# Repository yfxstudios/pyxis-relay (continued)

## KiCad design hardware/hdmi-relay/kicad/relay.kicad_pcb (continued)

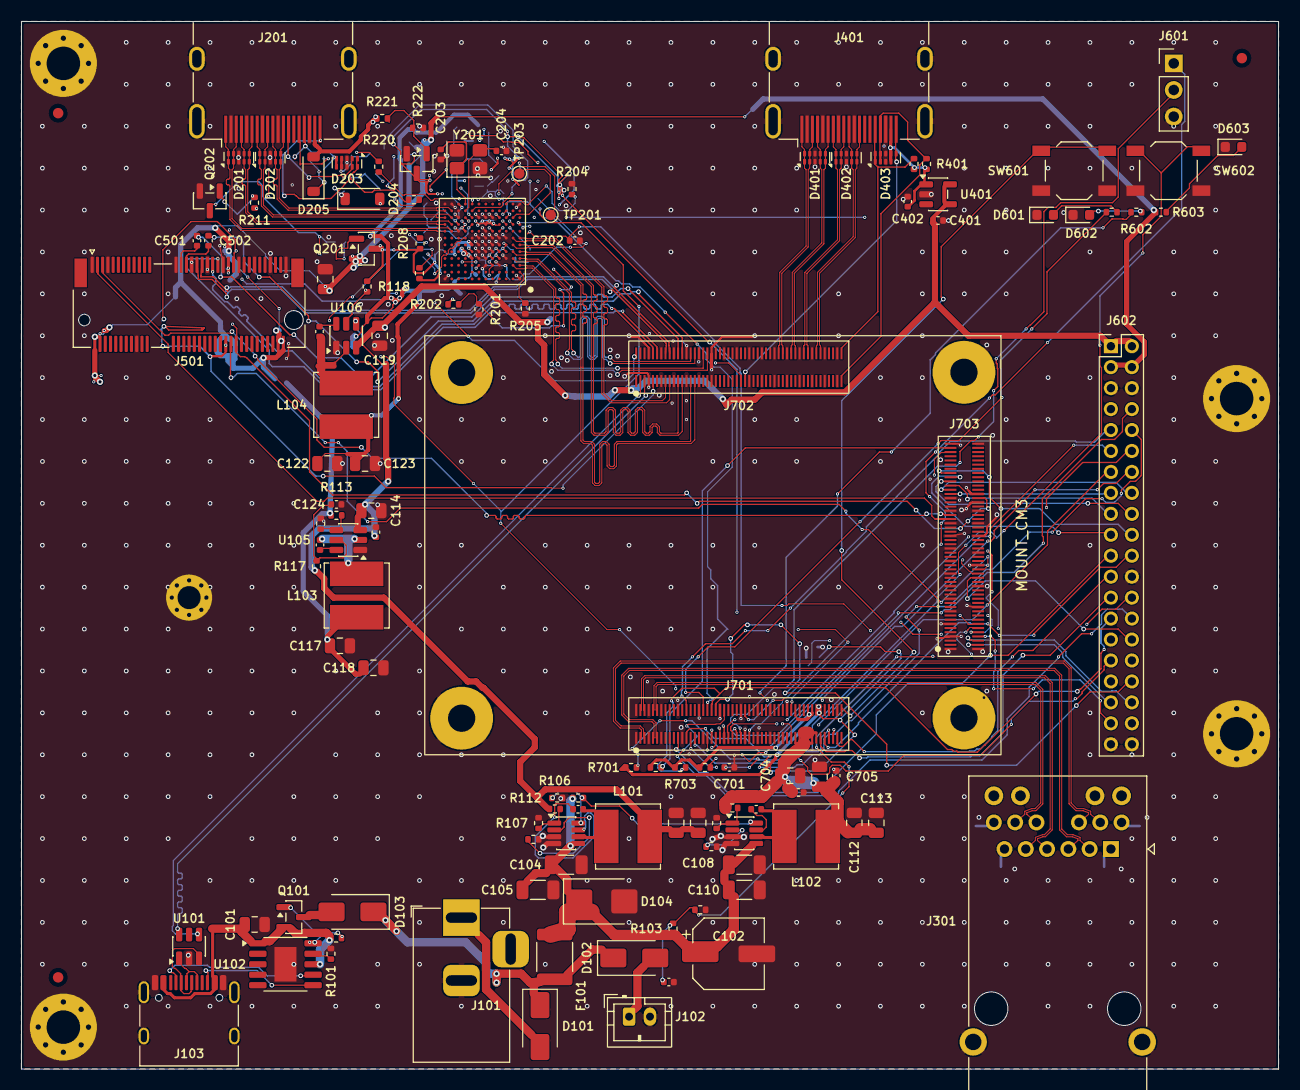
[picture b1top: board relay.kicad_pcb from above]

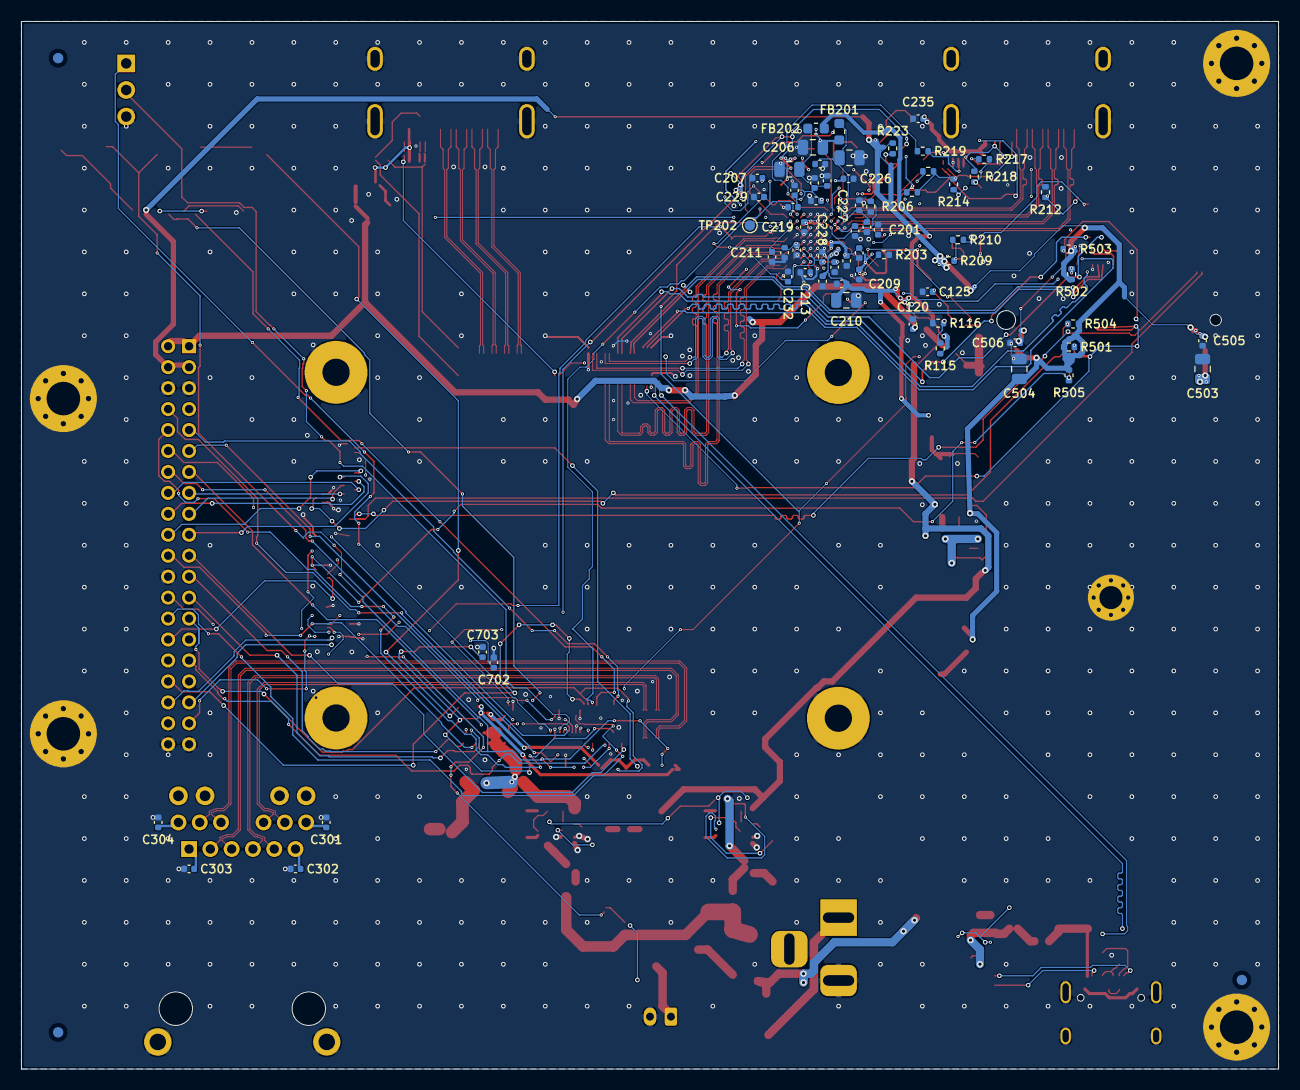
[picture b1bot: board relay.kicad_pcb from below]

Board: 4 copper layers, 120.0 x 100.0 mm, 198 parts (68 on the bottom side), 170 nets.

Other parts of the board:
C301, C302, C303, C304: 1uF; C_0402_1005Metric
FID1, FID2, FID3, FID4, FID5, FID6: Fiducial_1mm_Mask2mm
J301: RJ45 1000BASE-T magjack; RJ45_Pulse_JK0654219NL_Horizontal
MOUNT_CM3: Radxa CM3; Radxa_CM3_Mount

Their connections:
/Ethernet/CT1: C301.1, J301.12
/Ethernet/CT2: C302.1, J301.6
/Ethernet/CT3: C303.1, J301.1
/Ethernet/CT4: C304.1, J301.7
GND: C301.2, C302.2, C303.2, C304.2, J301.SH, MOUNT_CM3.MH1, MOUNT_CM3.MH2, MOUNT_CM3.MH3, MOUNT_CM3.MH4; also elsewhere on the board
MDI0_N: J301.10; also elsewhere on the board
MDI0_P: J301.11; also elsewhere on the board
MDI1_N: J301.5; also elsewhere on the board
MDI1_P: J301.4; also elsewhere on the board
MDI2_N: J301.2; also elsewhere on the board
MDI2_P: J301.3; also elsewhere on the board
MDI3_N: J301.9; also elsewhere on the board
MDI3_P: J301.8; also elsewhere on the board

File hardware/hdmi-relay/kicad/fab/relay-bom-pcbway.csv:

Line#,Qty,Designator,MPN,Manufacturer,Description,Package,Type,LCSC
1,1,C101,CL21B105KBFNNNE,Samsung Electro-Mechanics,1uF/50V: CAP CER 1uF 50V X7R 0805,C_0805_2012Metric,SMD,C28323
2,1,C102,RVT35V47M6X8,JIERR,47uF/35V: CAP ALUM 47uF ±20% 35V SMD,CP_Elec_6.3x7.7,SMD,C47023116
3,37,"C103,C115,C116,C120,C121,C124,C125,C201,C202,C207,C208,C209,C211,C212,C213,C214,C215,C216,C217,C218,C219,C223,C224,C225,C227,C228,C229,C230,C231,C232,C235,C505,C506,C702,C703,C706,C707",CL05B104KB54PNC,Samsung Electro-Mechanics,100nF: CAP CER 100nF 50V X7R 0402,C_0402_1005Metric,SMD,C307331
4,4,"C104,C105,C109,C110",1206B475K500NT,FH,4.7uF/50V: CAP CER 4.7uF 50V X7R 1206,C_1206_3216Metric,SMD,C29823
5,2,"C106,C111",CL05B103KB5NNNC,Samsung Electro-Mechanics,10nF: CAP CER 10nF 50V X7R 0402,C_0402_1005Metric,SMD,C15195
6,12,"C107,C108,C112,C113,C117,C118,C122,C123,C503,C504,C704,C705",CL21A226MAQNNNE,Samsung Electro-Mechanics,22uF/10V: CAP CER 22uF 25V X5R 0805,C_0805_2012Metric,SMD,C45783
7,7,"C114,C119,C205,C206,C210,C222,C234",CL21A106KAYNNNE,Samsung Electro-Mechanics,10uF/10V: CAP CER 10uF 25V X5R 0805,C_0805_2012Metric,SMD,C15850
8,2,"C203,C204",0402CG180J500NT,FH,18pF: CAP CER 18pF 50V C0G 0402,C_0402_1005Metric,SMD,C1549
9,10,"C220,C221,C226,C233,C301,C302,C303,C304,C401,C402",CL05A105KA5NQNC,Samsung Electro-Mechanics,1uF: CAP CER 1uF 25V X5R 0402,C_0402_1005Metric,SMD,C52923
10,2,"C501,C502",0402WGF0000TCE,UNI-ROYAL,0R: RES 0R jumper 62.5mW 0402,C_0402_1005Metric,SMD,C17168
11,1,C701,0402B102K500NT,FH,1nF: CAP CER 1nF 50V X7R 0402,C_0402_1005Metric,SMD,C1523
12,3,"D101,D102,D103",SS54,MDD(Microdiode Semiconductor),SS54: DIODE SCHOTTKY 40V SMA(DO-214AC),D_SMA,SMD,C22452
13,1,D104,SMBJ20CA,MDD(Microdiode Semiconductor),SMBJ20CA: TVS DIODE 20VWM 32.4VC DO-214AA(SMB),D_SMB,SMD,C113992
14,6,"D201,D202,D203,D401,D402,D403",RCLAMP0524P,TECH PUBLIC,RCLAMP0524P: ESD DIODE 5VWM 17VC DFN2510-10,USON-10_2.5x1.0mm_P0.5mm,SMD,C907837
15,2,"D204,D205",MBR0530T1G,onsemi,MBR0530: DIODE SCHOTTKY 30V SOD-123,D_SOD-123,SMD,C82046
16,1,D601,KT-0603W,Hubei KENTO Elec,white: LED WHITE 0603 SMD,LED_0603_1608Metric,SMD,C2290
17,1,D602,KT-0603B,Hubei KENTO Elec,blue: LED BLUE WATER CLEAR 0603 SMD,LED_0603_1608Metric,SMD,C2288
18,1,D603,KT-0603R,Hubei KENTO Elec,red PWR: LED RED WATER CLEAR 0603 SMD,LED_0603_1608Metric,SMD,C2286
19,1,F101,1812L300/30GR,LUTE,3A hold: PTC RESET FUSE 30V 3A 1812,Fuse_1812_4532Metric,SMD,C48985875
20,2,"FB201,FB202",MPZ1608S331ATA00,TDK,330R@100MHz: FERRITE BEAD 330Ω 0603 1LN,L_0603_1608Metric,SMD,C275487
21,1,J101,PJ-002AH,CUI,DC 6-17V: Right Angle DC Power Jack -25℃~+85℃ 2mm 6.5mm 5A 24V Through Hole Power Connectors RoHS,BarrelJack_Horizontal,THT,C2961147
22,1,J102,B2B-PH-K-S(LF)(SN),JST,NP-F plate: CONN HEADER TH 2POS 2mm,JST_PH_B2B-PH-K_1x02_P2.00mm_Vertical,THT,C131337
23,1,J103,TYPE-C-31-M-12,Korean Hroparts Elec,USB_C_Receptacle_USB2.0_16P: CONN RCPT Type-C 16POS SMD,USB_C_Receptacle_HRO_TYPE-C-31-M-12,SMD,C165948
24,2,"J201,J401",2086581001,MOLEX,HDMI IN: HDMI FOR INSERT-MOLD TYPE,HDMI_A_Molex_208658-1001_Horizontal,SMD,C916313
25,1,J501,2199230-4,TE Connectivity,M.2 E-key 2230: CONN 67POS 0.5mm SMD R/A,TE_M.2_E_2x38-1MP_P0.5mm,SMD,C2977809
26,1,J601,PZ254V-11-03P,XFCN,DEBUG UART 3V3: CONN HEADER 3POS 2.54mm SINGLE ROW TH,PinHeader_1x03_P2.54mm_Vertical,THT,C2937625
27,3,"J701,J702,J703",DF40C-100DS-0.4V(51),HRS,"CM3 J69: 0.4mm Pitch, 1.5 to 4.0mm Height, Board-to-Board and Board-to-FPC Connectors",Radxa_CM3_J69,SMD,C597931
28,2,"L101,L102",SRN6045TA-6R8M,BOURNS,"6.8uH 3.6A: FIXED IND 6.8uH 3.6A 34mΩ SMD,6x6mm",L_Bourns_SRN6045TA,SMD,C2041457
29,1,L103,SWPA6045S2R2NT,Sunlord,2.2uH: 2.2uH 4.6A 18mOhm ±30% 6x6 shielded power inductor,L_Bourns_SRN6045TA,SMD,C36500
30,1,L104,SWPA6045S1R5NT,Sunlord,1.5uH: 1.5uH 4.95A 12mOhm ±30% 6x6 shielded power inductor,L_Bourns_SRN6045TA,SMD,C96956
31,2,"Q101,Q201",AO3401A,AOS,AO3401A: MOSFET P-CH 30V 4A SOT-23,SOT-23,SMD,C15127
32,2,"Q202,Q203",MMBT3904(RANGE:100-300),JSCJ,MMBT3904: TRANS NPN 40V 200mA SOT-23,SOT-23,SMD,C20526
33,1,R101,0402WGF6801TCE,UNI-ROYAL,6.8k: RES 6.8kΩ ±1% 62.5mW 0402,R_0402_1005Metric,SMD,C25917
34,5,"R102,R103,R111,R117,R212",0402WGF1003TCE,UNI-ROYAL,100k: RES 100kΩ ±1% 62.5mW 0402,R_0402_1005Metric,SMD,C25741
35,11,"R104,R114,R115,R118,R201,R209,R222,R223,R504,R701,R702",0402WGF1002TCE,UNI-ROYAL,10k: RES 10kΩ ±1% 62.5mW 0402,R_0402_1005Metric,SMD,C25744
36,2,"R105,R108",0402WGF2003TCE,UNI-ROYAL,200k: RES 200k 1% 62.5mW 0402,R_0402_1005Metric,SMD,C25764
37,2,"R106,R109",0402WGF1103TCE,UNI-ROYAL,110k: RES 110kΩ ±1% 62.5mW 0402,R_0402_1005Metric,SMD,C25745
38,2,"R107,R110",0402WGF1502TCE,UNI-ROYAL,15k: RES 15kΩ ±1% 62.5mW 0402,R_0402_1005Metric,SMD,C25756
39,1,R112,0402WGF3902TCE,UNI-ROYAL,39k: RES 39kΩ ±1% 62.5mW 0402,R_0402_1005Metric,SMD,C25783
40,1,R113,0402WGF3302TCE,UNI-ROYAL,33k: RES 33kΩ ±1% 62.5mW 0402,R_0402_1005Metric,SMD,C25779
41,1,R116,0402WGF2322TCE,UNI-ROYAL,23.2k: RES 23.2kΩ ±1% 62.5mW 0402,R_0402_1005Metric,SMD,C25873
42,3,"R203,R204,R221",0402WGF2001TCE,UNI-ROYAL,2k 1%: RES 2kΩ ±1% 62.5mW 0402,R_0402_1005Metric,SMD,C4109
43,1,R205,0402WGF4021TCE,UNI-ROYAL,4.02k 1%: RES 4.02kΩ ±1% 62.5mW 0402,R_0402_1005Metric,SMD,C43251
44,1,R206,0402WGF1000TCE,UNI-ROYAL,100R: RES 100Ω ±1% 62.5mW 0402,R_0402_1005Metric,SMD,C25076
45,2,"R207,R208",0402WGF4701TCE,UNI-ROYAL,4.7k: RES 4.7kΩ ±1% 62.5mW 0402,R_0402_1005Metric,SMD,C25900
46,2,"R210,R211",0402WGF1001TCE,UNI-ROYAL,1k: RES 1kΩ ±1% 62.5mW 0402,R_0402_1005Metric,SMD,C11702
47,4,"R213,R215,R219,R220",0402WGF220JTCE,UNI-ROYAL,22R: RES 22Ω ±1% 62.5mW 0402,R_0402_1005Metric,SMD,C25092
48,1,R214,0402WGF2702TCE,UNI-ROYAL,27k: RES 27kΩ ±1% 62.5mW 0402,R_0402_1005Metric,SMD,C25771
49,2,"R217,R218",0402WGF4702TCE,UNI-ROYAL,47k: RES 47kΩ ±1% 62.5mW 0402,R_0402_1005Metric,SMD,C25792
50,5,"R401,R402,R603,R703,R704",0402WGF2201TCE,UNI-ROYAL,2.2k: RES 2.2kΩ ±1% 62.5mW 0402,R_0402_1005Metric,SMD,C25879
51,2,"R601,R602",0402WGF1500TCE,UNI-ROYAL,150R: RES 150R 1% 62.5mW 0402,R_0402_1005Metric,SMD,C25082
52,2,"SW601,SW602",TL3342F160QG,E-Switch,RESET: SWITCH TACTILE SPST 160gf SMD,SW_SPST_TL3342,SMD,C2886898
53,1,U101,USBLC6-2SC6,UMW,USBLC6-2SC6: ESD DIODE 15VC SOT-23-6,SOT-23-6,SMD,C2687116
54,1,U102,CH224A,WCH,CH224A: Power Receiver Controller 1C 140W ESSOP-10 Power Management - Specialized ,SSOP-10-1EP_3.9x4.9mm_P1mm_EP2.1x3.3mm,SMD,C42459160
55,2,"U103,U104",SY8303AIC,Silergy,"SY8303AIC: High Efficiency Fast Response, 3A, 40V Input Synchronous Step Down Regulator",TSOT-23-8,SMD,C97054
56,2,"U105,U106",TPS563201DDCR,TI,"TPS563201: 4.5-V to 17-V Input, 3-A Synchronous Step-Down Voltage Regulator",SOT-23-6,SMD,C116592
57,1,U201,RK628D,Rockchip,RK628D: LVDS -40℃~+125℃ WBBGA-144(8x8) Specialized RoHS,BGA-144_8.0x8.0mm_Layout12x12_P0.65mm,SMD,C2843533
58,1,U401,AP22804AW5-7,DIODES,AP22804AW5: Single Channel Power Distribution Load Switch,SOT-23-5,SMD,C3001659
59,1,Y201,X322524MOB4SI,YXC Crystal Oscillators,24MHz: CRYSTAL 24MHz 12pF SMD,Crystal_SMD_3225-4Pin_3.2x2.5mm,SMD,C70590
60,1,J301,JK0654219NL,PULSE,RJ45 1000BASE-T magjack: 1 Shielded Gold Phosphor Bronze 0℃~+70℃ Through Hole Modular/Ethernet Connector (RJ45) Jacks With Magnetics RoHS,RJ45_Pulse_JK0654219NL_Horizontal,THT,C3179417

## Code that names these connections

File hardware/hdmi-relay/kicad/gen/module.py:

"""Sheet: Radxa CM3 (RK3566) on three Hirose DF40 100-pin receptacles.

Pin names come from the Radxa CM3 datasheet rev 1.2, Appendix C (gen/cm3_pinout.json, extracted from
datasheets/Radxa_CM3_Datasheet.pdf), updated to module revision V1.32+ from Radxa's pinout change history
(datasheets/radxa_cm3_v1300_to_1320_pinout.xlsx). Older modules (V1.3, V1.31) differ on five pins. Radxa numbers J68's pins 101-200; on the receptacle footprint they are pads 1-100.
Every pin is either assigned below or marked unused (no-connect); the build fails on any pin left out.
"""
import json
import os

from parts import C0402, cap, resistor
from sch import box_symbol

PINOUT = json.load(open(os.path.join(os.path.dirname(os.path.abspath(__file__)), "cm3_pinout.json")))
GND = "GND"

# (connector, Radxa pin number) -> carrier net. Choices are explained in REV_A_SPEC.md section 7.
ASSIGN = {
    "J69": {
        3: "MDI3_P", 5: "MDI3_N", 4: "MDI1_P", 6: "MDI1_N", 11: "MDI2_P", 9: "MDI2_N", 12: "MDI0_P", 10: "MDI0_N",
        # the RK628D's I/O is 3.3 V. PMUIO2 (GPIO0_B0-D2) follows GPIO_VREF on the V1.322 module (R12/R24 0R), so it is
        # 3.3 V here, but its module pull-ups and 1.8 V builds (R11 fitted) keep the RK628D lines off it anyway
        76: "RK628D_PLUGIN_DET",                                     # GPIO0_A4 (PMUIO1, 3.3 V); SDMMC0_DET, an input
        35: "I2C_628_SCL", 36: "I2C_628_SDA",                       # I2C2_M1, GPIO4_B5/B4 (VCCIO6 = GPIO_VREF, 3.3 V)
        37: "SDI_UART_TX",                                           # GPIO4_C5 = UART9_TX_M1 (V1.32: was SARADC)
        93: "RECOVERY_ADC",                                          # SARADC_VIN0: low at boot = Rockusb recovery
        # GPIO0_D3-D6 (OSC) are 1.8 V only (CM3 schematic p.7); GPIO0_B0-D2 (PMUIO2) follow GPIO_VREF (3.3 V here,
        # first read as 1.8 V): the LEDs and every 3.3 V control line use VCCIO5/6/7 or PMUIO1 pins. PD_PG_N stays off
        # the module: GPIO0_B6 carries a 2.2k pull-up there, which held Q101 on.
        34: "LED_STATUS", 75: "LED_WIFI",                            # GPIO4_B1 (VCCIO6), GPIO0_A5 (PMUIO1)
        51: "DEBUG_RX", 55: "DEBUG_TX",                              # UART2_M0, the boot console
        100: "SOM_RESET_N",                                          # PMIC_RESET_KEY
        77: "5V_SOM", 79: "5V_SOM", 81: "5V_SOM", 83: "5V_SOM", 85: "5V_SOM", 87: "5V_SOM",
        78: "SOM_3V3", 84: "SOM_3V3", 86: "SOM_3V3",                # GPIO_VREF must tie to the module's +3V3
        88: "SOM_1V8", 90: "SOM_1V8",
        # DVP (CIF) for the SDI add-on header
        41: "DVP_D0", 49: "DVP_D1", 26: "DVP_D2", 25: "DVP_D3", 27: "DVP_D4", 45: "DVP_D5", 47: "DVP_D6",
        54: "DVP_D7", 21: "DVP_D14", 91: "DVP_D15", 89: "DVP_HSYNC", 95: "DVP_VSYNC", 97: "DVP_PCLK",
        38: "SDI_I2C_SCL", 44: "SDI_I2C_SDA",                       # I2C4_M0
        29: "SDI_GPIO1", 39: "SDI_GPIO3", 40: "SDI_GPIO4",           # 34 (was SDI_GPIO2) drives LED_STATUS
    },
    "J68": {
        103: "USB_OTG_DM", 105: "USB_OTG_DP",
        102: "PCIE_CLKREQ_N", 109: "PCIE_PERST_N",                  # PCIE20_*_M2 group (WAKE is J1 pin 38)
        110: "PCIE_REFCLK_P", 112: "PCIE_REFCLK_N", 116: "PCIE_RX_P", 118: "PCIE_RX_N",
        122: "PCIE_TX_P", 124: "PCIE_TX_N",
        117: "CSI_D0_P", 115: "CSI_D0_N", 123: "CSI_D1_P", 121: "CSI_D1_N", 129: "CSI_CLK_P", 127: "CSI_CLK_N",
        130: "CSI_D2_P", 128: "CSI_D2_N", 136: "CSI_D3_P", 134: "CSI_D3_N",
        170: "HDMITX_D2_P", 172: "HDMITX_D2_N", 176: "HDMITX_D1_P", 178: "HDMITX_D1_N",
        182: "HDMITX_D0_P", 184: "HDMITX_D0_N", 188: "HDMITX_CLK_P", 190: "HDMITX_CLK_N",
        153: "HDMITX_HPD", 199: "HDMITX_SDA", 200: "HDMITX_SCL",     # level-shifted on the module
        151: "CEC_GPIO",                                             # GPIO4_D1 (VCCIO7, 3.3 V): next to the RK628D
    },
    "J1": {
        40: "BT_DISABLE_N", 74: "WIFI_DISABLE_N", 38: "PCIE_WAKE_N",   # GPIO1_A4/B1 (VCCIO_ACODEC: 3.3 V in the DT), GPIO0_A0
        14: "VIN_SENSE",                                             # SARADC_VIN3, 0-1.8 V
        63: "USB_BT_DP", 65: "USB_BT_DM",                            # USB2 HOST2
        97: "OTG_VBUSDET",
        75: "DVP_D8", 77: "DVP_D9", 79: "DVP_D10", 81: "DVP_D11", 83: "DVP_D12", 85: "DVP_D13",
        36: "SDI_UART_RX",                                           # UART9_RX_M1 (TX is J69 pin 37)
        4: "SDI_GPIO5", 6: "SDI_GPIO6", 8: "SDI_GPIO7",              # GPIO3_A1/B4/C1 (VCCIO5 = 3.3 V)
        12: "RK628D_INT",                                            # GPIO3_C3 (VCCIO5 = 3.3 V)
        10: "RK628D_RESET_N",                                        # GPIO3_C2 (VCCIO5 = 3.3 V); was SDI_GPIO8
        95: "RK628D_PWR_EN",                                         # GPIO0_C4 (PMUIO2, 3.3 V) into an NPN base: fine
    },
}
OFFSET = {"J69": 0, "J68": 100, "J1": 0}


def _symbol(conn):
    pins = PINOUT[conn]
    rows = []
    for pad in range(1, 101):
        n = pad + OFFSET[conn]
        name = pins[str(n)]["name"] or "NC"
        ptype = "power_in" if name in ("+5V_INPUT", "GND") else "passive"
        rows.append((str(pad), f"{n} {name}" if OFFSET[conn] else name, ptype))
    return "relay:" + box_symbol(
        f"Radxa_CM3_{conn}", rows[0::2], rows[1::2], ref="J",
        footprint=f"relay:Radxa_CM3_{conn}", width=55.88,
        description=f"Radxa CM3 connector {conn} (carrier receptacle Hirose DF40C-100DS-0.4V(51), 1.5 mm stack). "
                    + ("Radxa pin = pad + 100." if OFFSET[conn] else "Radxa pin = pad."))


def build(project):
    from sch import Sheet
    s = Sheet(project, "module", "Module: Radxa CM3", 700, paper="A2")
    s.text("Radxa CM3 (RK3566, RM116-D2E16W0: 2 GB, 16 GB eMMC, no Wi-Fi) on three DF40C-100DS-0.4V(51) receptacles.\n"
           "Pinout for module revision V1.32 or later (shipping V1.322).  Power: 5V_SOM, 3.8-5.2 V, up to 3 A.\n"
           "GPIO_VREF tied to the module's +3V3 (3.3 V I/O, as the datasheet requires).  Unused pins are no-connect.\n"
           "The module has its own Ethernet PHY (RTL8211F) and level-shifts HDMI DDC/CEC/HPD.", (20, 15), 2)
    for i, conn in enumerate(("J69", "J68", "J1")):
        sym = _symbol(conn)
        assign = ASSIGN[conn]
        conns = {}
        for pad in range(1, 101):
            n = pad + OFFSET[conn]
            name = PINOUT[conn][str(n)]["name"]
            if n in assign:
                conns[str(pad)] = assign[n]
            elif name == "GND":
                conns[str(pad)] = GND
            else:
                conns[str(pad)] = None
        bad = set(assign) - {pad + OFFSET[conn] for pad in range(1, 101)}
        assert not bad, (conn, bad)
        s.add(sym, (110 + 170 * i, 200), conns, value=f"CM3 {conn}", ref="J",
              LCSC="C597931", Note="Hirose DF40C-100DS-0.4V(51) receptacle")

    # module support parts (datasheet sections 3.1, 3.2.1, 3.11)
    resistor(s, (60, 60), "SOM_1V8", "RECOVERY_ADC", "10k", Note="SARADC_VIN0 pull-up to 1.8 V (datasheet: keep it)")
    cap(s, (70, 60), "RECOVERY_ADC", "GND", "1nF")
    resistor(s, (85, 60), "SOM_3V3", "OTG_VBUSDET", "10k",
             Note="VBUSDET must be high (2.7-3.3 V) for USB device mode: held high so flashing always works")
    cap(s, (100, 60), "SOM_3V3", "GND", "100nF")
    cap(s, (110, 60), "SOM_1V8", "GND", "100nF")
    resistor(s, (150, 60), "SOM_3V3", "SDI_I2C_SCL", "2.2k")
    resistor(s, (160, 60), "SOM_3V3", "SDI_I2C_SDA", "2.2k")
    for i in range(4):
        cap(s, (180 + 10 * i, 60), "5V_SOM", "GND", "22uF/10V" if i < 2 else "100nF",
            footprint="Capacitor_SMD:C_0805_2012Metric" if i < 2 else C0402)
    s.flag("SOM_3V3", (240, 45))
    s.flag("SOM_1V8", (255, 45))
    return s

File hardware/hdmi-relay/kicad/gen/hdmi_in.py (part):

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        "HDMIRX_D2P": "HDMIRX_D2_P", "HDMIRX_D2N": "HDMIRX_D2_N",
        "HDMIRX_HPD": "RX_HPD", "HDMIRX_SCL": "RX_SCL", "HDMIRX_SDA": "RX_SDA", "HDMIRX_CEC": "RX_CEC",
        "HDMIRX_EXTR": "RX_EXTR", "OSC_IN": "XIN_628", "OSC_OUT": "XOUT_628", "RESETN": "RK628D_RESET_N",
        "TEST": "GND", "I2C_ADDR(GPIO3_B3)": "RK628D_I2C_ADDR", "I2C_SCL": "I2C_628_SCL", "I2C_SDA": "I2C_628_SDA",
        "INT(GPIO3_B4)": "RK628D_INT", "I2S_SCK": "I2S_628_SCLK", "I2S_LRCK": "I2S_628_LRCK", "I2S_D0": "I2S_628_SDO",
        "I2S_D1": None, "I2S_D2": None, "I2S_D3": None, "TEST_CLKO/I2S_MCLK": None, "GPIO1_A1": None,
        "MIPI_REXT": "MIPI_REXT", "HDMITX_EXTR": "TX_EXTR",
        "DVDD_1V1": "1V1_628", "PLL_AVDD_1V1": "AVDD_1V1_628", "HDMIRX_DVDD_1V1": "AVDD_1V1_628",
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    cap(s, (440, 100), "HDMIRX_5V", "GND", "100nF")
    # Lines in connector order (pins 1-12), so each ESD part sits across two neighbouring pairs and the board
    # routes them straight through
    for i, pins in enumerate((("HDMIRX_D2_P", "HDMIRX_D2_N", "HDMIRX_D1_P", "HDMIRX_D1_N"),
                              ("HDMIRX_D0_P", "HDMIRX_D0_N", "HDMIRX_CLK_P", "HDMIRX_CLK_N"),
                              ("PORT_HPD", "PORT_CEC", "PORT_SCL", "PORT_SDA"))):
        _rclamp(s, (360 + 30 * i, 250), pins)
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          footprint="Diode_SMD:D_SOD-123")
    resistor(s, (315, 190), "CEC_PU", "PORT_CEC", "27k")
    resistor(s, (330, 190), "RX_CEC", "PORT_CEC", "22R")
    resistor(s, (345, 190), "CEC_GPIO", "PORT_CEC", "0R", dnp=True,
             Note="Option: module GPIO bit-bangs CEC if the RK628D driver can't send Blackmagic vendor messages")
    # DDC: 47k pull-ups to the source's +5V through a Schottky; 22R series to the RK628D
    s.add("Device:D_Schottky", (300, 215), {"A": "HDMIRX_5V", "K": "DDC_PU"}, value="MBR0530",
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
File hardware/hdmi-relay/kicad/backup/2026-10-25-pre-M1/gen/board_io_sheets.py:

"""Sheets: HDMI out, M.2 Wi-Fi/Bluetooth, and board I/O (debug, buttons, LEDs, SDI header, mounting).
REV_A_SPEC.md section 5."""
from parts import C0402, C0805, LED0603, cap, resistor


def hdmi_out(project):
    from sch import Sheet
    s = Sheet(project, "hdmi_out", "HDMI out", 400)
    s.text("HDMI OUT from the module's HDMI 2.0 TX: the on-set monitor feed (captured frames, no encode).\n"
           "TMDS pairs 100 ohm differential.  5 V on pin 18 from a current-limited switch (HDMI requires >= 55 mA).\n"
           "DDC/HPD go straight to the module, which level-shifts them (Radxa CM3 datasheet 3.5.1).  CEC not used.",
           (20, 15), 2)
    s.add("Connector:HDMI_A", (300, 130),
          {"D2+": "HDMITX_D2_P", "D2-": "HDMITX_D2_N", "D1+": "HDMITX_D1_P", "D1-": "HDMITX_D1_N",
           "D0+": "HDMITX_D0_P", "D0-": "HDMITX_D0_N", "CK+": "HDMITX_CLK_P", "CK-": "HDMITX_CLK_N",
           "CEC": None, "UTILITY": None, "SCL": "HDMITX_SCL", "SDA": "HDMITX_SDA", "HPD": "HDMITX_HPD",
           "+5V": "HDMITX_5V", "D2S": "GND", "D1S": "GND", "D0S": "GND", "CKS": "GND", "GND": "GND", "SH": "GND"},
          value="HDMI OUT", footprint="Connector_Video:HDMI_A_Molex_208658-1001_Horizontal",
          Note="Same connector part as HDMI IN")
    from hdmi_in import _rclamp
    # lines in connector order (pins 1-12, then 15, 16, 18, 19), so each ESD part sits across neighbouring pins and
    # the board routes them straight through, as on HDMI IN
    _rclamp(s, (230, 230), ("HDMITX_D2_P", "HDMITX_D2_N", "HDMITX_D1_P", "HDMITX_D1_N"))
    _rclamp(s, (260, 230), ("HDMITX_D0_P", "HDMITX_D0_N", "HDMITX_CLK_P", "HDMITX_CLK_N"))
    _rclamp(s, (290, 230), ("HDMITX_SCL", "HDMITX_SDA", "HDMITX_5V", "HDMITX_HPD"))
    # 5 V to the monitor
    s.add("Power_Management:AP22804AW5", (100, 60), {"IN": "5V_SYS", "EN": "5V_SYS", "OUT": "HDMITX_5V",
                                                     "~{FLG}": None, "GND": "GND"},
          footprint="Package_TO_SOT_SMD:SOT-23-5", Note="Current-limited load switch")
    cap(s, (75, 75), "5V_SYS", "GND", "1uF")
    cap(s, (125, 75), "HDMITX_5V", "GND", "1uF")
    # The Radxa CM3 level-shifts DDC and CEC and has HPD's pull-down and series resistor on the module
    # (CM3 datasheet 3.5.1): DDC and HPD go straight to the connector. DDC pull-ups to the monitor's 5 V.
    resistor(s, (100, 150), "HDMITX_5V", "HDMITX_SCL", "2.2k")
    resistor(s, (110, 150), "HDMITX_5V", "HDMITX_SDA", "2.2k")
    return s


def m2(project):
    from sch import Sheet
    s = Sheet(project, "m2_wifi", "M.2 Wi-Fi + Bluetooth", 500)
    s.text("M.2 2230 E-key socket for the RTL8822CE card: Wi-Fi on PCIe x1 (combo PHY in PCIe mode), Bluetooth on\n"
           "USB 2.0.  Host-side 100 nF AC coupling on the lanes the host transmits.  PCIe 85 ohm, USB 90 ohm.", (20, 15), 2)
    conn = {
        "PETp0": "PCIE_RX_P", "PETn0": "PCIE_RX_N",            # card transmits -> host receives
        "PERp0": "M2_PER_P", "PERn0": "M2_PER_N",              # host transmits through the AC caps below
        "REFCLKp0": "PCIE_REFCLK_P", "REFCLKn0": "PCIE_REFCLK_N",
        "~{PERST0}": "PCIE_PERST_N", "~{CLKREQ0}": "PCIE_CLKREQ_N", "~{PEWAKE0}": "PCIE_WAKE_N",
        "~{W_DISABLE1}": "WIFI_DISABLE_N", "~{W_DISABLE2}": "BT_DISABLE_N",
        "USB_D+": "USB_BT_DP", "USB_D-": "USB_BT_DM", "3.3V": "3V3_IO", "GND": "GND",
    }
    for name in ("~{LED_1}", "PCM_CLK/I2S_SCK", "SDIO_CLK", "PCM_SYNC/I2S_WS", "SDIO_CMD", "PCM_IN/I2S_SD_IN",
                 "SDIO_DATA0", "PCM_OUT/I2S_SD_OUT", "SDIO_DATA1", "~{LED_2}", "SDIO_DATA2", "SDIO_DATA3",
                 "~{UART_WAKE}", "~{SDIO_WAKE}", "UART_RXD", "~{SDIO_RESET}", "UART_TXD", "UART_CTS", "UART_RTS",
                 "VENDOR_DEFINED", "COEX3", "COEX2", "COEX1", "SUSCLK", "I2C_DATA", "RESERVED/PETp1", "I2C_CLK",
                 "RESERVED/PETn1", "~{ALERT}", "RESERVED", "RESERVED/PERp1", "UIM_SWP/~{PERST1}", "RESERVED/PERn1",
                 "UIM_POWER_SNK/~{CLKREQ1}", "UIM_POWER_SRC/GPIO1/~{PEWAKE1}", "RESERVED/REFCLKp1",
                 "RESERVED/REFCLKn1"):
        conn[name] = None
    s.add("Connector:Bus_M.2_Socket_E", (200, 140), conn, value="M.2 E-key 2230",
          footprint="Connector_PCBEdge:TE_M.2_E_2x38-1MP_P0.5mm",
          Note="TE 2199230-4 (or 2199125/2199119 family): check the card stop line against its datasheet")
    # the 2230 card's hold-down: an M2 standoff (or nut and screw) at the card's far end, on GND
    s.add("Mechanical:MountingHole_Pad", (330, 140), {"1": "GND"}, ref="H", value="M.2 2230 standoff",
          footprint="MountingHole:MountingHole_2.2mm_M2_Pad_Via")
    # PCIe TX AC coupling is on the module (CM3 C54/C55, 100 nF): a second 100 nF here would leave 50 nF, under the
    # CEM minimum of 75 nF. C501/C502 are fitted as 0R links; 100 nF pads kept for rev B experiments.
    note = "0R link: the CM3 has the TX AC caps (C54/C55)"
    cap(s, (110, 90), "PCIE_TX_P", "M2_PER_P", "0R", Note=note)
    cap(s, (120, 90), "PCIE_TX_N", "M2_PER_N", "0R", Note=note)
    # PERST#, CLKREQ#, WAKE# and BT_DISABLE# (GPIO1_B2/B0/B1/A4) sit in VCCIO_ACODEC (RK817 LDO4), off until
    # software enables it: pull-ups to 3V3_IO would back-feed that bank through the pad clamps, so R501-R503 and R505
    # are not fitted. The SoC's own pulls take over once the device tree sets LDO4 to 3.3 V, always on (pinctrl:
    # pull-up on CLKREQ#/WAKE#, the card's open-drain outputs). PERST# rests on its reset pull-down (card held in
    # reset) and BT_DISABLE# reads low (Bluetooth off) until the driver runs. WIFI_DISABLE# (GPIO0_A0, PMUIO1) keeps
    # its pull-up.
    for i, net in enumerate(("PCIE_PERST_N", "PCIE_CLKREQ_N", "PCIE_WAKE_N", "WIFI_DISABLE_N", "BT_DISABLE_N")):
        resistor(s, (290 + 10 * i, 60), "3V3_IO", net, "10k", **({} if net == "WIFI_DISABLE_N" else {"dnp": True}))
    for i, v in enumerate(("22uF", "22uF", "100nF", "100nF")):
        cap(s, (290 + 10 * i, 230), "3V3_IO", "GND", v, footprint=C0805 if v == "22uF" else C0402)
    return s


def board_io(project):
    from sch import Sheet
    s = Sheet(project, "board_io", "Debug, buttons, LEDs, SDI header", 600)
    s.text("Debug UART (1.5 Mb/s), RESET and RECOVERY buttons, status LEDs, the SDI add-on header (not fitted)\n"
           "and mounting holes.  The SDI header carries the module's 16-bit DVP camera input (BT.1120 from an SDI\n"
           "receiver such as the GS2971A).  On the CM3 the DVP pins are free: its Ethernet uses GMAC1_M0.", (20, 15), 2)
    s.add("Connector_Generic:Conn_01x03", (40, 60), {"Pin_1": "DEBUG_TX", "Pin_2": "DEBUG_RX", "Pin_3": "GND"},
          value="DEBUG UART 1V8", ref="J", Note="1.8 V levels (GPIO0_D0/D1 are in the CM3's 1.8 V PMUIO2): use a 1.8 V adapter", footprint="Connector_PinHeader_2.54mm:PinHeader_1x03_P2.54mm_Vertical")
    # buttons
    s.add("Switch:SW_Push", (100, 60), {"1": "SOM_RESET_N", "2": "GND"}, value="RESET",
          footprint="Button_Switch_SMD:SW_SPST_TL3342")
    s.add("Switch:SW_Push", (100, 90), {"1": "RECOVERY_ADC", "2": "GND"}, value="RECOVERY",
          footprint="Button_Switch_SMD:SW_SPST_TL3342",
          Note="Held at power-up: Rockusb recovery for flashing over USB-C (CM3 datasheet 3.11)")
    # LEDs: GPIO high = on, from 3.3 V CM3 pins; 150R gives about 2-3 mA through a white or blue LED
    for i, (net, col) in enumerate((("LED_STATUS", "white"), ("LED_WIFI", "blue"))):
        x = 180 + 30 * i
        resistor(s, (x, 60), net, f"{net}_A", "150R")
        s.add("Device:LED", (x + 12, 80), {"A": f"{net}_A", "K": "GND"}, value=col, footprint=LED0603)
    resistor(s, (250, 60), "3V3_IO", "LED_PWR_A", "2.2k")
    s.add("Device:LED", (262, 80), {"A": "LED_PWR_A", "K": "GND"}, value="red PWR", footprint=LED0603)
    # SDI add-on header
    pins = ["5V_SYS", "5V_SYS", "3V3_IO", "3V3_IO", "GND", "GND"]
    pins += [f"DVP_D{i}" for i in range(16)] + ["DVP_PCLK", "GND", "DVP_HSYNC", "DVP_VSYNC"]
    pins += ["SDI_I2C_SCL", "SDI_I2C_SDA", "SDI_UART_TX", "SDI_UART_RX"] + ["SDI_GPIO1", None] + [f"SDI_GPIO{i}" for i in range(3, 8)] + [None]
    # pins 32 and 38 unused: their CM3 pins now drive LED_STATUS and reset the RK628D (Oct 25 level fixes)
    pins += ["GND", "GND"]
    assert len(pins) == 40
    s.add("Connector_Generic:Conn_02x20_Odd_Even", (330, 140), {str(i + 1): n for i, n in enumerate(pins)},
          value="SDI add-on (DNP)", ref="J", dnp=True,
          footprint="Connector_PinHeader_2.00mm:PinHeader_2x20_P2.00mm_Vertical")
    for i in range(4):
        s.add("Mechanical:MountingHole_Pad", (60 + 15 * i, 200), {"1": "GND"}, ref="H",
              footprint="MountingHole:MountingHole_3.2mm_M3_Pad_Via")
    return s

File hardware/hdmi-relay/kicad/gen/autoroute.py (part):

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

# ------------------------------------------------------------------ stages
TO_J69 = ["RK628D_INT", "RK628D_PLUGIN_DET", "RK628D_RESET_N", "I2C_628_SCL", "I2C_628_SDA", "CEC_GPIO",
          "RK628D_PWR_EN"]


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

def stage_repin(board, B, R):
    """RK628D_INT and RK628D_PWR_EN move from J69 (J701) pins 46 and 24 to J1 (J703) pins 93 and 95 (gen/module.py):
    the pads change nets, the two nets' copper outside the RK628D corner comes out (the corner's escape stays),
    and stage gaps joins them to the new pins."""
    moves = {("J701", "46"): None, ("J701", "24"): None, ("J703", "93"): "RK628D_INT", ("J703", "95"): "RK628D_PWR_EN"}
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

def stage_placefix(board, B, R):
    """Moves the parts in PLACEFIX (and C702/C703 next to the CM3's SOM_3V3/SOM_1V8 pins, on the back), with
    the copper that touched their pads taken out first; their nets are joined again afterwards (stage
    gaps/route_net) and GND pads get vias."""
    moved = [m[0] for m in PLACEFIX] + ["C702", "C703"]
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            f.SetOrientationDegrees(rot)
            f.SetPosition(B.mm(x, y))
    R.changed()
    # C702/C703: on the back, as near the SOM_3V3 / SOM_1V8 pins' vias as there is room
    for ref, net in (("C702", "SOM_3V3"), ("C703", "SOM_1V8")):
        pins = [p for p in board.FindFootprintByReference("J701").Pads() if short(p.GetNetname()) == net]
        tx = sum(B.xy(p)[0] for p in pins) / len(pins)
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    (place_near), and the 1V1_628 copper left beside L104's turned switch pad comes out."""
    y = board.FindFootprintByReference("Y201")
    yp = {p.GetNumber(): B.xy(p) for p in y.Pads()}
    for ref, net, pin, gnd in (("C203", "XIN_628", "1", "4"), ("C204", "XOUT_628", "3", "2")):
        f = board.FindFootprintByReference(ref)
        f.SetPosition(B.mm(200, 200))              # off the board while its spot is chosen
        R.changed()
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
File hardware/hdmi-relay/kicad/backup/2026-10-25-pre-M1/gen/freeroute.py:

"""Finishes chosen nets on the routed board with Freerouting, then runs gen/finish.py's steps.

  /Applications/KiCad/KiCad.app/Contents/Frameworks/Python.framework/Versions/Current/bin/python3 gen/freeroute.py

Needs Java 21+ and the Freerouting jar (FREEROUTING below; Freerouting 2.5.0 from its GitHub releases).

Freerouting can't be told to route only some nets, so the export hides the others: every existing track and via is
locked (exported as protected, so Freerouting leaves them alone), every net not in TARGET is split into single-pin
nets (still obstacles, nothing to route), and the inner planes are exported as power layers. Only Freerouting's new
copper on the TARGET nets is added to the board, on the outer layers.
"""
import os
import shutil
import subprocess
import sys

import pcbnew

HERE = os.path.dirname(os.path.abspath(__file__))
ROOT = os.path.dirname(HERE)
sys.path.insert(0, HERE)
from finish import ROUTED, OUT, finish  # noqa: E402

JAVA = "/opt/homebrew/opt/openjdk/bin/java"
FREEROUTING = os.path.expanduser("~/tools/freerouting/freerouting-2.5.0.jar")
WORK = os.path.join(ROOT, "freerouting")
# the RK628D connections gen/route.py's own router leaves open
TARGET = {"XOUT_628", "RX_SDA", "RX_CEC", "EFUSE_628", "I2S_628_MCLK", "I2C_628_SCL", "I2C_628_SDA", "CEC_GPIO",
          "RK628D_PWR_EN", "1V1_628", "AVDD_3V3_628", "AVDD_1V1_628"}


def short(name):
    return name.split("/")[-1]


def key(t):
    s, e = t.GetStart(), t.GetEnd()
    return (t.GetClass(), t.GetLayer(), t.GetNetCode(), s.x, s.y, e.x, e.y)


def load():
    # the board takes its net classes and rules from the project file beside it
    shutil.copy(os.path.join(ROOT, "relay.kicad_pro"), ROUTED.replace(".kicad_pcb", ".kicad_pro"))
    return pcbnew.LoadBoard(ROUTED)


os.makedirs(WORK, exist_ok=True)
dsn, ses = os.path.join(WORK, "relay.dsn"), os.path.join(WORK, "relay.ses")

board = load()
before = {key(t) for t in board.GetTracks()}
for t in board.GetTracks():
    t.SetLocked(True)
for layer in (pcbnew.In1_Cu, pcbnew.In2_Cu):
    board.SetLayerType(layer, pcbnew.LT_POWER)
if not pcbnew.ExportSpecctraDSN(board, dsn):
    raise SystemExit("DSN export failed")

# Only the target nets are left for Freerouting to route: every other net is split into single-pin nets in the
# export, so its pads and tracks stay obstacles with a net and a clearance, but it has nothing to connect. (Routing
# all 250 open connections took Freerouting over 20 minutes; moving the other nets to "no net" instead made
# Freerouting ignore them as obstacles.)
import re  # noqa: E402
text = open(dsn).read()


def split(m):
    name, pins = m.group(1), m.group(2).split()
    if short(name.strip('"')) in TARGET or len(pins) < 2:
        return m.group(0)
    base = name.strip('"')
    out = f'(net {name}\n      (pins {pins[0]})\n    )'
    for k, pin in enumerate(pins[1:], 2):
        out += f'\n    (net "{base}__{k}"\n      (pins {pin})\n    )'
    return out


text = re.sub(r'\(net ("[^"]*"|\S+)\n\s+\(pins ([^)]*)\)\n\s+\)', split, text)
open(dsn, "w").write(text)

if os.path.exists(ses):
    os.remove(ses)
log = os.path.join(WORK, "freerouting.log")   # follow progress with: tail -f freerouting/freerouting.log
with open(log, "w") as f:
    subprocess.run([JAVA, "-jar", FREEROUTING, "-de", dsn, "-do", ses, "-mp", "8", "--gui.enabled=false"],
                   stdout=f, stderr=subprocess.STDOUT, timeout=1200)
if not os.path.exists(ses):
    raise SystemExit(f"Freerouting wrote no session; see {log}")

# Bring back only Freerouting's new copper on the target nets. (KiCad's own session import replaces every track on
# the board, and with the other nets hidden in the export their routing would come back without nets.)
from sexpr import find, find_all, parse  # noqa: E402
board = load()
existing = [t for t in board.GetTracks()]
LAYERS = {"F.Cu": pcbnew.F_Cu, "B.Cu": pcbnew.B_Cu, "In1.Cu": pcbnew.In1_Cu, "In2.Cu": pcbnew.In2_Cu}


def pos(x, y):   # session units are 0.1 um, y up; the board's are nm, y down
    return pcbnew.VECTOR2I(int(x) * 100, -int(y) * 100)


def have_track(layer, nc, a, b):
    for t in existing:
        if t.GetClass() == "PCB_TRACK" and t.GetLayer() == layer and t.GetNetCode() == nc:
            s_, e_ = t.GetStart(), t.GetEnd()
            if ((abs(s_.x - a.x) + abs(s_.y - a.y) < 2000 and abs(e_.x - b.x) + abs(e_.y - b.y) < 2000) or
                    (abs(s_.x - b.x) + abs(s_.y - b.y) < 2000 and abs(e_.x - a.x) + abs(e_.y - a.y) < 2000)):
                return True
    return False


def have_via(nc, at):
    return any(t.GetClass() == "PCB_VIA" and t.GetNetCode() == nc and
               abs(t.GetPosition().x - at.x) + abs(t.GetPosition().y - at.y) < 2000 for t in existing)


tree = parse(open(ses).read())
added = skipped_inner = 0
for n in find_all(find(find(tree, "routes"), "network_out"), "net"):
    name = n[1]
    if short(name) not in TARGET:
        continue
    ni = board.FindNet(name)
    nc = ni.GetNetCode()
    for w in find_all(n, "wire"):
        path = find(w, "path")
        layer, width, xy = LAYERS[path[1]], int(path[2]) * 100, path[3:]
        pts = [pos(xy[k], xy[k + 1]) for k in range(0, len(xy) - 1, 2)]
        for a, b in zip(pts, pts[1:]):
            if have_track(layer, nc, a, b):
                continue
            if layer in (pcbnew.In1_Cu, pcbnew.In2_Cu):   # the inner layers stay planes
                skipped_inner += 1
                continue
            t = pcbnew.PCB_TRACK(board)
            t.SetStart(a); t.SetEnd(b); t.SetWidth(width); t.SetLayer(layer); t.SetNet(ni)
            board.Add(t)
            added += 1
    for v in find_all(n, "via"):
        at = pos(v[2], v[3])
        if have_via(nc, at):
            continue
        d, drill = (int(x) for x in v[1].split("_")[1].split(":"))   # "Via[0-3]_450:250_um"
        via = pcbnew.PCB_VIA(board)
        via.SetPosition(at); via.SetViaType(pcbnew.VIATYPE_THROUGH); via.SetLayerPair(pcbnew.F_Cu, pcbnew.B_Cu)
        via.SetWidth(d * 1000); via.SetDrill(drill * 1000); via.SetNet(ni)
        board.Add(via)
        added += 1
print(f"Freerouting: added {added} new tracks and vias on the target nets ({skipped_inner} inner-layer segments "
      f"left out)")
pcbnew.SaveBoard(ROUTED, board)
finish(board)
pcbnew.SaveBoard(OUT, board)
